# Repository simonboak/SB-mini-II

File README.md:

# SB mini II
A homebrewed Apple II clone. [Read more on the blog post](https://unimplementedtrap.com/sb-mini-ii-apple-ii-clone/)

## Hardware Overview

- The CPU is a standard 65C02 running at near 1.024 MHz (the original Apple II ran at 1.023 for the 60 Hz models), after dividing the 4.096 MHz crystal by 4.
- The 12kB ROM image is placed on the 32k EEPROM. Because there's spare room on this chip a jumper allows for selecting the high or low half of the ROM chip, so I've placed Ardian Black's [Deadtest](https://github.com/misterblack1/appleII_deadtest) program in there.
- 48kB of RAM is accomplished by using one and half 32kB SRAM chips. Figured this was easier to use matching chipd than it was to use a 32kb + 16kB chip.
- Address decoding works exactly like the real Apple II. This was mostly based on the schematics in _Understanding The Apple II_ by Jim Sather.
- In Addition to the I/O slots, this has:
  - Speaker: matching the genuine Apple II
  - Game I/O: as the NE558 quad timer is hard to find, I've [implemented this replacement using a pair of 556 chips](https://github.com/roybaer/ne558_replacement).
  - Keyboard: a Raspberry Pi Pico provides a modern USB interface but electrically it connects to the Apple II in the same way as the original ASCII keyboard did. The Pi can also generate a reset pulse when pressing Control + Print Screen, and also performs a power-on reset for the system. The firmware for this is [in this project here](https://github.com/simonboak/SB-mini-II-Keyboard).
  - Graphics: there is absolutely no onboard hardware for displaying graphics. Instead you'll want to use an [Apple VGA Card](https://github.com/markadev/AppleII-VGA).
- Features deliberately missing:
  - Expansion slots do not provide the DMA, USER 1 or 7M clock signals.
  - The bus is not buffered: with a CMOS design this is less likely to be a problem (although no guarantees for interfacing with cards using 74LS logic).
  - There is no cassette input or output.
- These are the Revision 1 files. Rev 0 was a smaller board with no 5V regulation, only 7 slots and 32k on board RAM. The plan had been to leave out slot 0 and work out how to make full use of a second 32k RAM chip to have the full 64k without needing a language card, however this almost doubled the amount of circuitry needed.

## 3D Printed Case

Combining the design of the Apple II with the ProFile hard disk, the case requires a bit of assembly:

1. Print each piece with the flat side on the print bad (you could print the lid pieces as one if desired)
2. Glue the "tongue" into the slot along the bottom inside edge of the front piece. This will locate into the notch inside the front of the base.
3. Glue the top, front and sides together.
4. For the light pipe it was filled with hot glue to create a diffused lense with the LED glued in behind.
5. The base requires 8x M3 threaded inserts, 2 of which are for the back panel, the rest are the PCB mounts.
6. The 20mm speaker can be taped into the round hole in the base.

### Rear with reset switch

An alernative file for the rear panel of the case is included. This contains a 7mm hole for a suitably sized push button switch.

### Rev 1 Update:

Alternative files are provided for the lid: this greatly reduces the radius of the curve on the front of the case. This should print better and without requiring so much filling and sanding, although it does depart from the styling inspiration of the ProFile hard disk.

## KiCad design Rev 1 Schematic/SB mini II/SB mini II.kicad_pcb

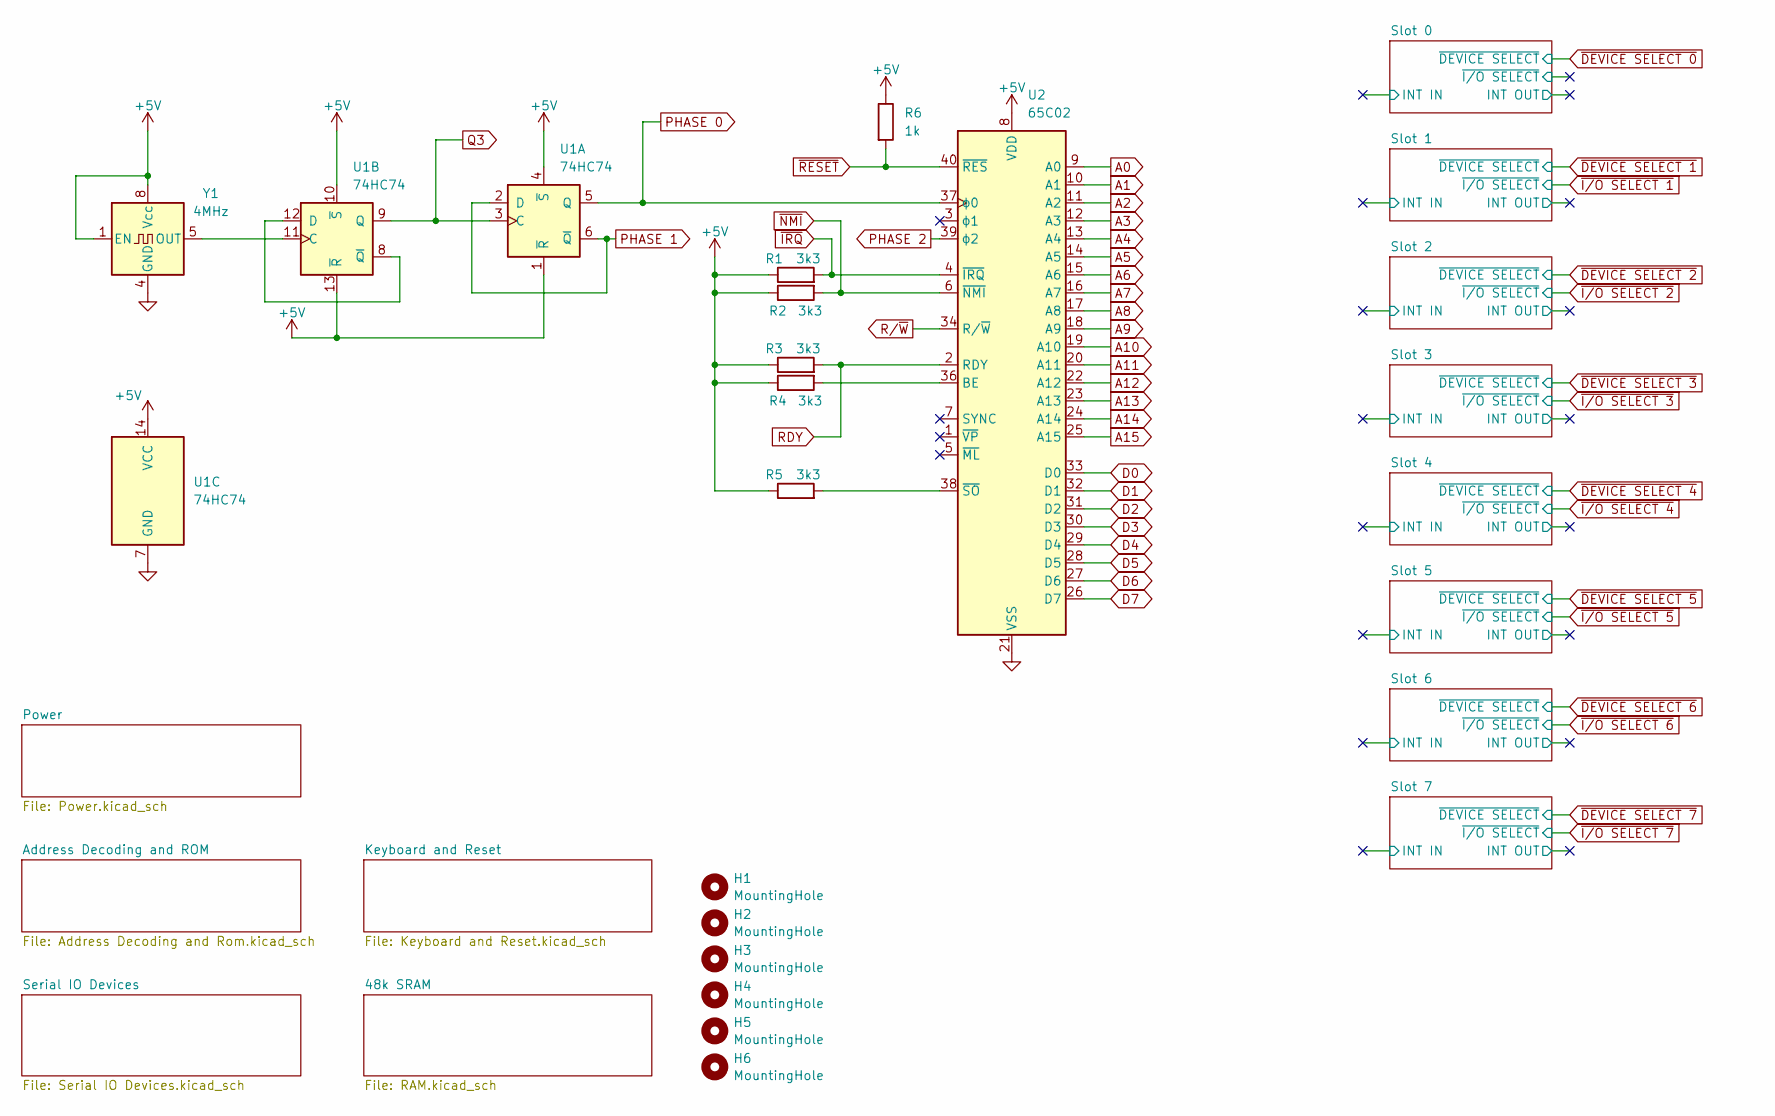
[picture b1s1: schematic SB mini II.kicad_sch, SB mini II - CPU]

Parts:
H1, H2, H3, H4, H5, H6: MountingHole; MountingHole_3.2mm_M3
R1, R2, R3, R4, R5: 3k3; R_Axial_DIN0207_L6.3mm_D2.5mm_P7.62mm_Horizontal
R6: 1k; R_Axial_DIN0207_L6.3mm_D2.5mm_P7.62mm_Horizontal
U1: 74HC74; DIP-14_W7.62mm_LongPads
U2: 65C02; DIP-40_W15.24mm
Y1: 4MHz; Oscillator_DIP-8

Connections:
+5V: R1.1, R2.1, R3.1, R4.1, R5.1, R6.1, U1.1 (~R), U1.4 (~S), U1.10 (~S), U1.13 (~R), U1.14 (VCC), U2.8 (VDD), Y1.1 (EN), Y1.8 (Vcc); also elsewhere on the board
A0: U2.9 (A0); also elsewhere on the board
A1: U2.10 (A1); also elsewhere on the board
A2: U2.11 (A2); also elsewhere on the board
A3: U2.12 (A3); also elsewhere on the board
A4: U2.13 (A4); also elsewhere on the board
A5: U2.14 (A5); also elsewhere on the board
A6: U2.15 (A6); also elsewhere on the board
A7: U2.16 (A7); also elsewhere on the board
A8: U2.17 (A8); also elsewhere on the board
A9: U2.18 (A9); also elsewhere on the board
A10: U2.19 (A10); also elsewhere on the board
A11: U2.20 (A11); also elsewhere on the board
A12: U2.22 (A12); also elsewhere on the board
A13: U2.23 (A13); also elsewhere on the board
A14: U2.24 (A14); also elsewhere on the board
A15: U2.25 (A15); also elsewhere on the board
D0: U2.33 (D0); also elsewhere on the board
D1: U2.32 (D1); also elsewhere on the board
D2: U2.31 (D2); also elsewhere on the board
D3: U2.30 (D3); also elsewhere on the board
D4: U2.29 (D4); also elsewhere on the board
D5: U2.28 (D5); also elsewhere on the board
D6: U2.27 (D6); also elsewhere on the board
D7: U2.26 (D7); also elsewhere on the board
GND: U1.7 (GND), U2.21 (VSS), Y1.4 (GND); also elsewhere on the board
unnamed: U1.11 (C), Y1.5 (OUT)
unnamed: U1.8 (~Q), U1.12 (D)
unnamed: R4.2, U2.36 (BE)
unnamed: R5.2, U2.38 (~SO)
PHASE 0: U1.5 (Q), U2.37 (ϕ0); also elsewhere on the board
PHASE 1: U1.2 (D), U1.6 (~Q); also elsewhere on the board
PHASE 2: U2.39 (ϕ2); also elsewhere on the board
Q3: U1.3 (C), U1.9 (Q); also elsewhere on the board
RDY: R3.2, U2.2 (RDY); also elsewhere on the board
R/~W: U2.34 (R/~W); also elsewhere on the board
~IRQ: R1.2, U2.4 (~IRQ); also elsewhere on the board
~NMI: R2.2, U2.6 (~NMI); also elsewhere on the board
~RESET: R6.2, U2.40 (~RES); also elsewhere on the board

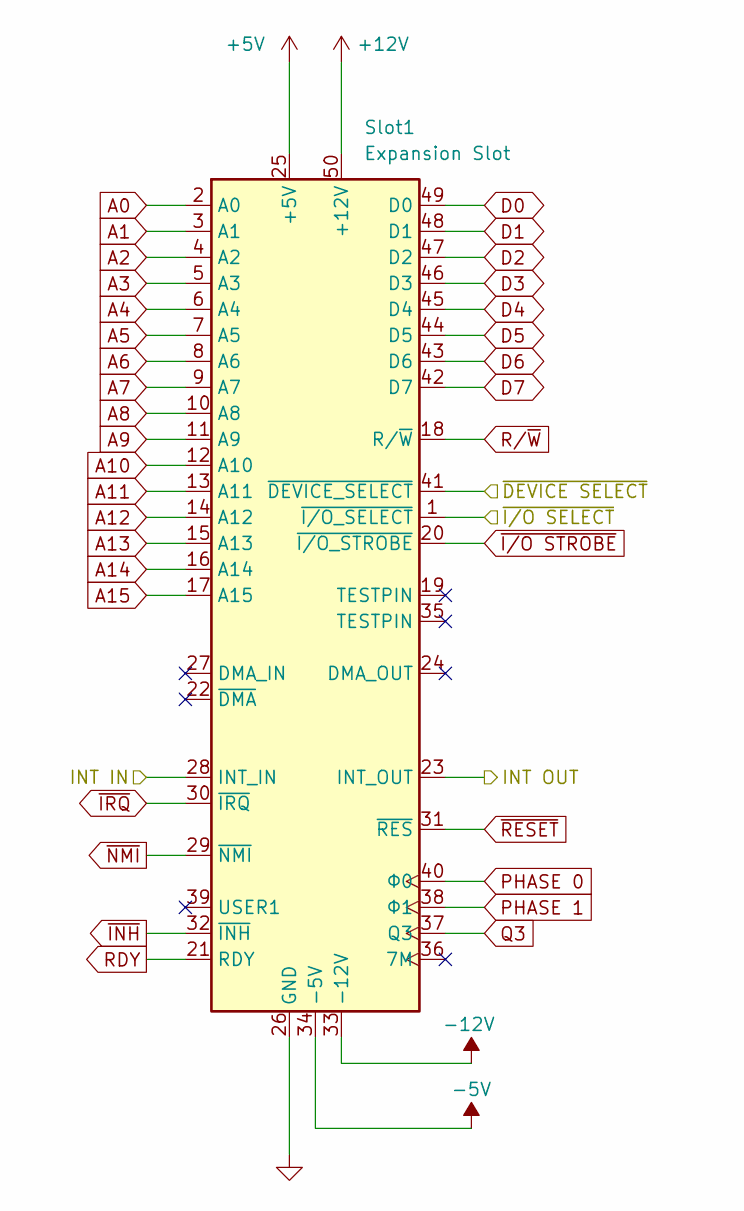
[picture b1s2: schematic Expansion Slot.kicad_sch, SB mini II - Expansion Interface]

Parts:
Slot1: Expansion Slot; EDAC_395-050-520-201_CounterClockwise

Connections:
+5V: Slot1.25 (+5V); also elsewhere on the board
+12V: Slot1.50 (+12V); also elsewhere on the board
-5V: Slot1.34 (-5V); also elsewhere on the board
-12V: Slot1.33 (-12V); also elsewhere on the board
/Slot 1/INT IN: Slot1.28 (INT_IN)
/Slot 1/INT OUT: Slot1.23 (INT_OUT)
A0: Slot1.2 (A0); also elsewhere on the board
A1: Slot1.3 (A1); also elsewhere on the board
A2: Slot1.4 (A2); also elsewhere on the board
A3: Slot1.5 (A3); also elsewhere on the board
A4: Slot1.6 (A4); also elsewhere on the board
A5: Slot1.7 (A5); also elsewhere on the board
A6: Slot1.8 (A6); also elsewhere on the board
A7: Slot1.9 (A7); also elsewhere on the board
A8: Slot1.10 (A8); also elsewhere on the board
A9: Slot1.11 (A9); also elsewhere on the board
A10: Slot1.12 (A10); also elsewhere on the board
A11: Slot1.13 (A11); also elsewhere on the board
A12: Slot1.14 (A12); also elsewhere on the board
A13: Slot1.15 (A13); also elsewhere on the board
A14: Slot1.16 (A14); also elsewhere on the board
A15: Slot1.17 (A15); also elsewhere on the board
D0: Slot1.49 (D0); also elsewhere on the board
D1: Slot1.48 (D1); also elsewhere on the board
D2: Slot1.47 (D2); also elsewhere on the board
D3: Slot1.46 (D3); also elsewhere on the board
D4: Slot1.45 (D4); also elsewhere on the board
D5: Slot1.44 (D5); also elsewhere on the board
D6: Slot1.43 (D6); also elsewhere on the board
D7: Slot1.42 (D7); also elsewhere on the board
GND: Slot1.26 (GND); also elsewhere on the board
PHASE 0: Slot1.40 (Φ0); also elsewhere on the board
PHASE 1: Slot1.38 (Φ1); also elsewhere on the board
Q3: Slot1.37 (Q3); also elsewhere on the board
RDY: Slot1.21 (RDY); also elsewhere on the board
R/~W: Slot1.18 (R/~W); also elsewhere on the board
~DEVICE SELECT 1: Slot1.41 (~DEVICE_SELECT); also elsewhere on the board
~INH: Slot1.32 (~INH); also elsewhere on the board
~IRQ: Slot1.30 (~IRQ); also elsewhere on the board
~I/O SELECT 1: Slot1.1 (~I/O_SELECT); also elsewhere on the board
~I/O STROBE: Slot1.20 (~I/O_STROBE); also elsewhere on the board
~NMI: Slot1.29 (~NMI); also elsewhere on the board
~RESET: Slot1.31 (~RES); also elsewhere on the board

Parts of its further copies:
Slot0, Slot2, Slot3, Slot4, Slot5, Slot6, Slot7: Expansion Slot; EDAC_395-050-520-201_CounterClockwise

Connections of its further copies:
+5V: Slot0.25 (+5V), Slot2.25 (+5V), Slot3.25 (+5V), Slot4.25 (+5V), Slot5.25 (+5V), Slot6.25 (+5V), Slot7.25 (+5V); also elsewhere on the board
+12V: Slot0.50 (+12V), Slot2.50 (+12V), Slot3.50 (+12V), Slot4.50 (+12V), Slot5.50 (+12V), Slot6.50 (+12V), Slot7.50 (+12V); also elsewhere on the board
-5V: Slot0.34 (-5V), Slot2.34 (-5V), Slot3.34 (-5V), Slot4.34 (-5V), Slot5.34 (-5V), Slot6.34 (-5V), Slot7.34 (-5V); also elsewhere on the board
-12V: Slot0.33 (-12V), Slot2.33 (-12V), Slot3.33 (-12V), Slot4.33 (-12V), Slot5.33 (-12V), Slot6.33 (-12V), Slot7.33 (-12V); also elsewhere on the board
/Slot 0/INT IN: Slot0.28 (INT_IN)
/Slot 0/INT OUT: Slot0.23 (INT_OUT)
/Slot 0/~I/O SELECT: Slot0.1 (~I/O_SELECT)
/Slot 2/INT IN: Slot2.28 (INT_IN)
/Slot 2/INT OUT: Slot2.23 (INT_OUT)
/Slot 3/INT IN: Slot4.28 (INT_IN)
/Slot 3/INT OUT: Slot4.23 (INT_OUT)
/Slot 4/INT IN: Slot5.28 (INT_IN)
/Slot 4/INT OUT: Slot5.23 (INT_OUT)
/Slot 5/INT IN: Slot3.28 (INT_IN)
/Slot 5/INT OUT: Slot3.23 (INT_OUT)
/Slot 6/INT IN: Slot6.28 (INT_IN)
/Slot 6/INT OUT: Slot6.23 (INT_OUT)
/Slot 7/INT IN: Slot7.28 (INT_IN)
/Slot 7/INT OUT: Slot7.23 (INT_OUT)
A0: Slot0.2 (A0), Slot2.2 (A0), Slot3.2 (A0), Slot4.2 (A0), Slot5.2 (A0), Slot6.2 (A0), Slot7.2 (A0); also elsewhere on the board
A1: Slot0.3 (A1), Slot2.3 (A1), Slot3.3 (A1), Slot4.3 (A1), Slot5.3 (A1), Slot6.3 (A1), Slot7.3 (A1); also elsewhere on the board
A2: Slot0.4 (A2), Slot2.4 (A2), Slot3.4 (A2), Slot4.4 (A2), Slot5.4 (A2), Slot6.4 (A2), Slot7.4 (A2); also elsewhere on the board
A3: Slot0.5 (A3), Slot2.5 (A3), Slot3.5 (A3), Slot4.5 (A3), Slot5.5 (A3), Slot6.5 (A3), Slot7.5 (A3); also elsewhere on the board
A4: Slot0.6 (A4), Slot2.6 (A4), Slot3.6 (A4), Slot4.6 (A4), Slot5.6 (A4), Slot6.6 (A4), Slot7.6 (A4); also elsewhere on the board
A5: Slot0.7 (A5), Slot2.7 (A5), Slot3.7 (A5), Slot4.7 (A5), Slot5.7 (A5), Slot6.7 (A5), Slot7.7 (A5); also elsewhere on the board
A6: Slot0.8 (A6), Slot2.8 (A6), Slot3.8 (A6), Slot4.8 (A6), Slot5.8 (A6), Slot6.8 (A6), Slot7.8 (A6); also elsewhere on the board
A7: Slot0.9 (A7), Slot2.9 (A7), Slot3.9 (A7), Slot4.9 (A7), Slot5.9 (A7), Slot6.9 (A7), Slot7.9 (A7); also elsewhere on the board
A8: Slot0.10 (A8), Slot2.10 (A8), Slot3.10 (A8), Slot4.10 (A8), Slot5.10 (A8), Slot6.10 (A8), Slot7.10 (A8); also elsewhere on the board
A9: Slot0.11 (A9), Slot2.11 (A9), Slot3.11 (A9), Slot4.11 (A9), Slot5.11 (A9), Slot6.11 (A9), Slot7.11 (A9); also elsewhere on the board
A10: Slot0.12 (A10), Slot2.12 (A10), Slot3.12 (A10), Slot4.12 (A10), Slot5.12 (A10), Slot6.12 (A10), Slot7.12 (A10); also elsewhere on the board
A11: Slot0.13 (A11), Slot2.13 (A11), Slot3.13 (A11), Slot4.13 (A11), Slot5.13 (A11), Slot6.13 (A11), Slot7.13 (A11); also elsewhere on the board
A12: Slot0.14 (A12), Slot2.14 (A12), Slot3.14 (A12), Slot4.14 (A12), Slot5.14 (A12), Slot6.14 (A12), Slot7.14 (A12); also elsewhere on the board
A13: Slot0.15 (A13), Slot2.15 (A13), Slot3.15 (A13), Slot4.15 (A13), Slot5.15 (A13), Slot6.15 (A13), Slot7.15 (A13); also elsewhere on the board
A14: Slot0.16 (A14), Slot2.16 (A14), Slot3.16 (A14), Slot4.16 (A14), Slot5.16 (A14), Slot6.16 (A14), Slot7.16 (A14); also elsewhere on the board
A15: Slot0.17 (A15), Slot2.17 (A15), Slot3.17 (A15), Slot4.17 (A15), Slot5.17 (A15), Slot6.17 (A15), Slot7.17 (A15); also elsewhere on the board
D0: Slot0.49 (D0), Slot2.49 (D0), Slot3.49 (D0), Slot4.49 (D0), Slot5.49 (D0), Slot6.49 (D0), Slot7.49 (D0); also elsewhere on the board
D1: Slot0.48 (D1), Slot2.48 (D1), Slot3.48 (D1), Slot4.48 (D1), Slot5.48 (D1), Slot6.48 (D1), Slot7.48 (D1); also elsewhere on the board
D2: Slot0.47 (D2), Slot2.47 (D2), Slot3.47 (D2), Slot4.47 (D2), Slot5.47 (D2), Slot6.47 (D2), Slot7.47 (D2); also elsewhere on the board
D3: Slot0.46 (D3), Slot2.46 (D3), Slot3.46 (D3), Slot4.46 (D3), Slot5.46 (D3), Slot6.46 (D3), Slot7.46 (D3); also elsewhere on the board
D4: Slot0.45 (D4), Slot2.45 (D4), Slot3.45 (D4), Slot4.45 (D4), Slot5.45 (D4), Slot6.45 (D4), Slot7.45 (D4); also elsewhere on the board
D5: Slot0.44 (D5), Slot2.44 (D5), Slot3.44 (D5), Slot4.44 (D5), Slot5.44 (D5), Slot6.44 (D5), Slot7.44 (D5); also elsewhere on the board
D6: Slot0.43 (D6), Slot2.43 (D6), Slot3.43 (D6), Slot4.43 (D6), Slot5.43 (D6), Slot6.43 (D6), Slot7.43 (D6); also elsewhere on the board
D7: Slot0.42 (D7), Slot2.42 (D7), Slot3.42 (D7), Slot4.42 (D7), Slot5.42 (D7), Slot6.42 (D7), Slot7.42 (D7); also elsewhere on the board
GND: Slot0.26 (GND), Slot2.26 (GND), Slot3.26 (GND), Slot4.26 (GND), Slot5.26 (GND), Slot6.26 (GND), Slot7.26 (GND); also elsewhere on the board
PHASE 0: Slot0.40 (Φ0), Slot2.40 (Φ0), Slot3.40 (Φ0), Slot4.40 (Φ0), Slot5.40 (Φ0), Slot6.40 (Φ0), Slot7.40 (Φ0); also elsewhere on the board
PHASE 1: Slot0.38 (Φ1), Slot2.38 (Φ1), Slot3.38 (Φ1), Slot4.38 (Φ1), Slot5.38 (Φ1), Slot6.38 (Φ1), Slot7.38 (Φ1); also elsewhere on the board
Q3: Slot0.37 (Q3), Slot2.37 (Q3), Slot3.37 (Q3), Slot4.37 (Q3), Slot5.37 (Q3), Slot6.37 (Q3), Slot7.37 (Q3); also elsewhere on the board
RDY: Slot0.21 (RDY), Slot2.21 (RDY), Slot3.21 (RDY), Slot4.21 (RDY), Slot5.21 (RDY), Slot6.21 (RDY), Slot7.21 (RDY); also elsewhere on the board
R/~W: Slot0.18 (R/~W), Slot2.18 (R/~W), Slot3.18 (R/~W), Slot4.18 (R/~W), Slot5.18 (R/~W), Slot6.18 (R/~W), Slot7.18 (R/~W); also elsewhere on the board
~DEVICE SELECT 0: Slot0.41 (~DEVICE_SELECT); also elsewhere on the board
~DEVICE SELECT 2: Slot2.41 (~DEVICE_SELECT); also elsewhere on the board
~DEVICE SELECT 3: Slot4.41 (~DEVICE_SELECT); also elsewhere on the board
~DEVICE SELECT 4: Slot5.41 (~DEVICE_SELECT); also elsewhere on the board
~DEVICE SELECT 5: Slot3.41 (~DEVICE_SELECT); also elsewhere on the board
~DEVICE SELECT 6: Slot6.41 (~DEVICE_SELECT); also elsewhere on the board
~DEVICE SELECT 7: Slot7.41 (~DEVICE_SELECT); also elsewhere on the board
~INH: Slot0.32 (~INH), Slot2.32 (~INH), Slot3.32 (~INH), Slot4.32 (~INH), Slot5.32 (~INH), Slot6.32 (~INH), Slot7.32 (~INH); also elsewhere on the board
~IRQ: Slot0.30 (~IRQ), Slot2.30 (~IRQ), Slot3.30 (~IRQ), Slot4.30 (~IRQ), Slot5.30 (~IRQ), Slot6.30 (~IRQ), Slot7.30 (~IRQ); also elsewhere on the board
~I/O SELECT 2: Slot2.1 (~I/O_SELECT); also elsewhere on the board
~I/O SELECT 3: Slot4.1 (~I/O_SELECT); also elsewhere on the board
~I/O SELECT 4: Slot5.1 (~I/O_SELECT); also elsewhere on the board
~I/O SELECT 5: Slot3.1 (~I/O_SELECT); also elsewhere on the board
~I/O SELECT 6: Slot6.1 (~I/O_SELECT); also elsewhere on the board
~I/O SELECT 7: Slot7.1 (~I/O_SELECT); also elsewhere on the board
~I/O STROBE: Slot0.20 (~I/O_STROBE), Slot2.20 (~I/O_STROBE), Slot3.20 (~I/O_STROBE), Slot4.20 (~I/O_STROBE), Slot5.20 (~I/O_STROBE), Slot6.20 (~I/O_STROBE), Slot7.20 (~I/O_STROBE); also elsewhere on the board
~NMI: Slot0.29 (~NMI), Slot2.29 (~NMI), Slot3.29 (~NMI), Slot4.29 (~NMI), Slot5.29 (~NMI), Slot6.29 (~NMI), Slot7.29 (~NMI); also elsewhere on the board
~RESET: Slot0.31 (~RES), Slot2.31 (~RES), Slot3.31 (~RES), Slot4.31 (~RES), Slot5.31 (~RES), Slot6.31 (~RES), Slot7.31 (~RES); also elsewhere on the board

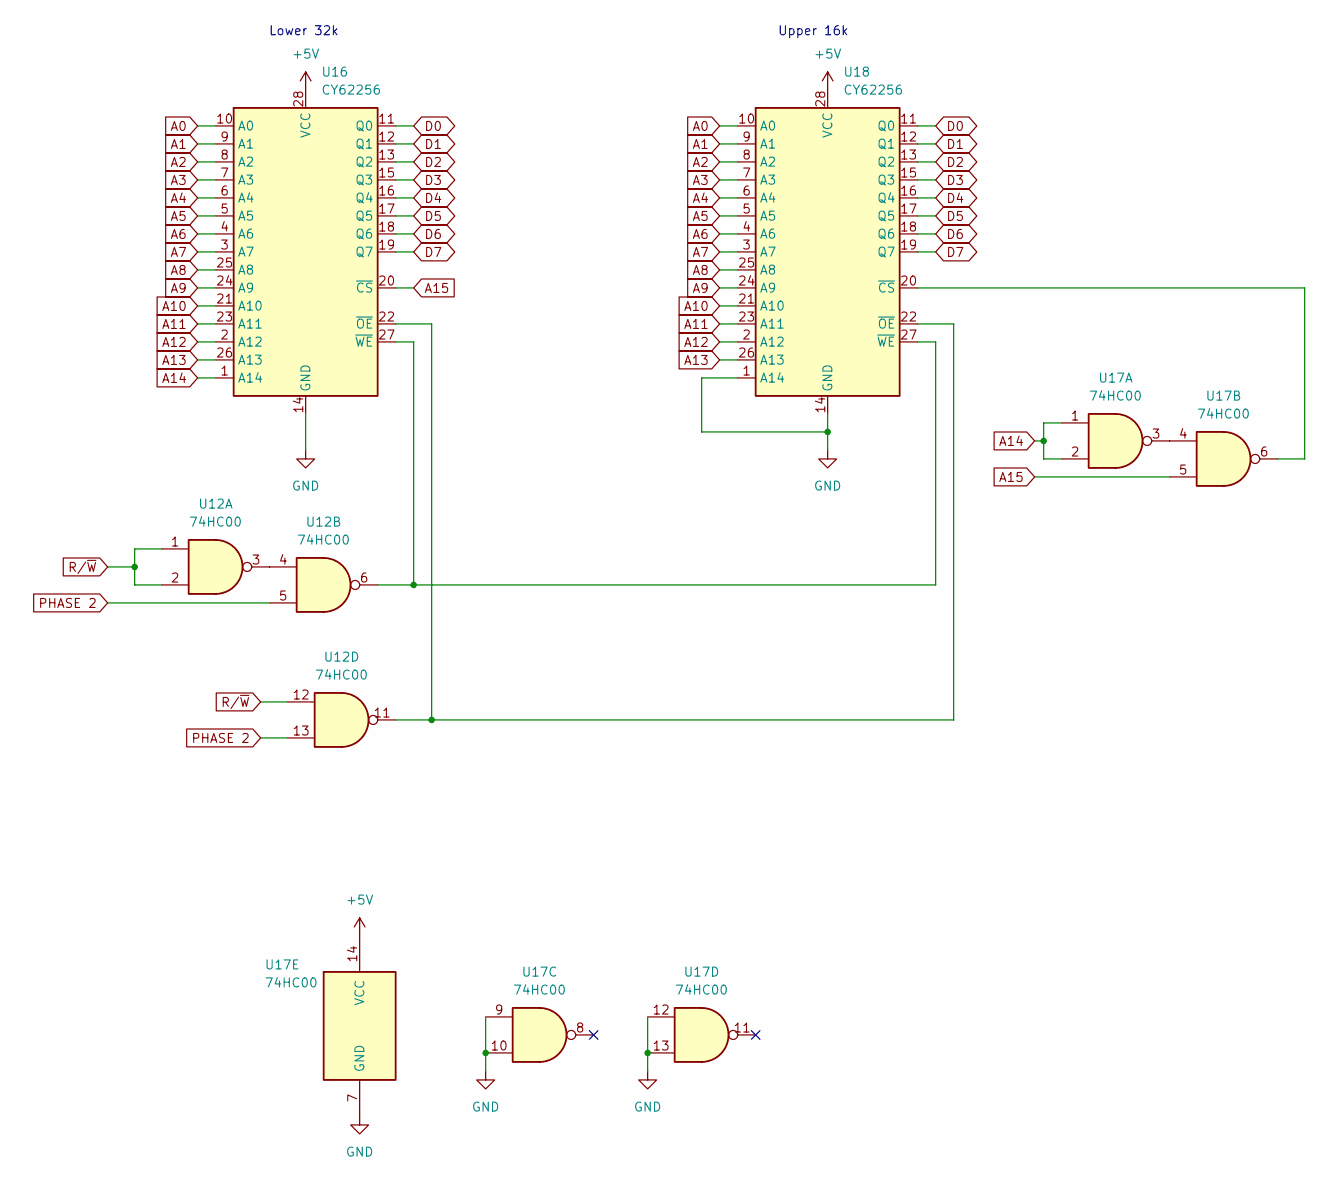
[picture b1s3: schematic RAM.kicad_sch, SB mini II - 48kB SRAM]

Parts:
U12, U17: 74HC00; DIP-14_W7.62mm_LongPads
U16, U18: CY62256; DIP-28_W7.62mm_LongPads

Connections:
+5V: U16.28 (VCC), U17.14 (VCC), U18.28 (VCC); also elsewhere on the board
A0: U16.10 (A0), U18.10 (A0); also elsewhere on the board
A1: U16.9 (A1), U18.9 (A1); also elsewhere on the board
A2: U16.8 (A2), U18.8 (A2); also elsewhere on the board
A3: U16.7 (A3), U18.7 (A3); also elsewhere on the board
A4: U16.6 (A4), U18.6 (A4); also elsewhere on the board
A5: U16.5 (A5), U18.5 (A5); also elsewhere on the board
A6: U16.4 (A6), U18.4 (A6); also elsewhere on the board
A7: U16.3 (A7), U18.3 (A7); also elsewhere on the board
A8: U16.25 (A8), U18.25 (A8); also elsewhere on the board
A9: U16.24 (A9), U18.24 (A9); also elsewhere on the board
A10: U16.21 (A10), U18.21 (A10); also elsewhere on the board
A11: U16.23 (A11), U18.23 (A11); also elsewhere on the board
A12: U16.2 (A12), U18.2 (A12); also elsewhere on the board
A13: U16.26 (A13), U18.26 (A13); also elsewhere on the board
A14: U16.1 (A14), U17.1, U17.2; also elsewhere on the board
A15: U16.20 (~CS), U17.5; also elsewhere on the board
D0: U16.11 (Q0), U18.11 (Q0); also elsewhere on the board
D1: U16.12 (Q1), U18.12 (Q1); also elsewhere on the board
D2: U16.13 (Q2), U18.13 (Q2); also elsewhere on the board
D3: U16.15 (Q3), U18.15 (Q3); also elsewhere on the board
D4: U16.16 (Q4), U18.16 (Q4); also elsewhere on the board
D5: U16.17 (Q5), U18.17 (Q5); also elsewhere on the board
D6: U16.18 (Q6), U18.18 (Q6); also elsewhere on the board
D7: U16.19 (Q7), U18.19 (Q7); also elsewhere on the board
GND: U16.14 (GND), U17.7 (GND), U17.9, U17.10, U17.12, U17.13, U18.1 (A14), U18.14 (GND); also elsewhere on the board
unnamed: U12.3, U12.4
unnamed: U12.11, U16.22 (~OE), U18.22 (~OE)
unnamed: U12.6, U16.27 (~WE), U18.27 (~WE)
unnamed: U17.3, U17.4
unnamed: U17.6, U18.20 (~CS)
PHASE 2: U12.5, U12.13; also elsewhere on the board
R/~W: U12.1, U12.2, U12.12; also elsewhere on the board

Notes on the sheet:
Upper 16k
Lower 32k

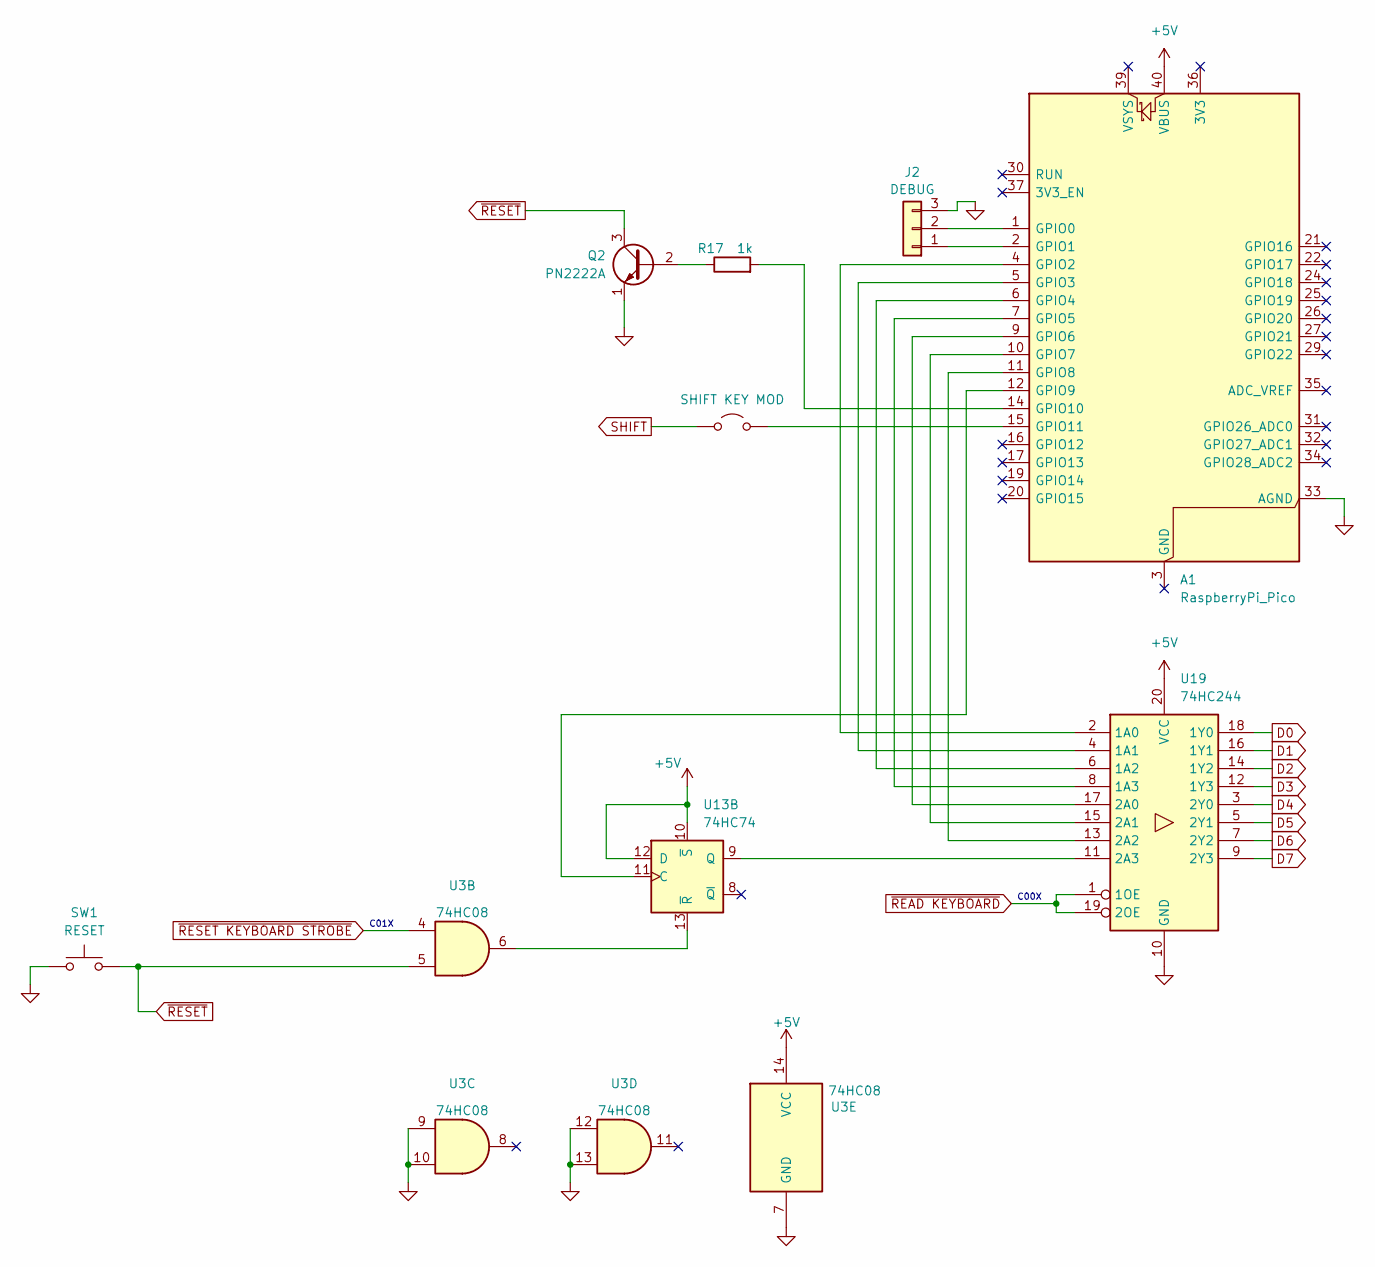
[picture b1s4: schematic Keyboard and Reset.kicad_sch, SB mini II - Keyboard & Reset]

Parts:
A1: RaspberryPi_Pico; RaspberryPi_Pico_Common_Unspecified
J2: DEBUG; PinHeader_1x03_P2.54mm_Vertical
JP2: SHIFT KEY MOD; TestPoint_2Pads_Pitch2.54mm_Drill0.8mm
Q2: PN2222A; TO-92L_HandSolder
R17: 1k; R_Axial_DIN0207_L6.3mm_D2.5mm_P7.62mm_Horizontal
SW1: RESET; SW_PUSH_1P1T_6x3.5mm_H5.0_APEM_MJTP1250
U3: 74HC08; DIP-14_W7.62mm_LongPads
U13: 74HC74; DIP-14_W7.62mm_LongPads
U19: 74HC244; DIP-20_W7.62mm_LongPads

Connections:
+5V: A1.40 (VBUS), U3.14 (VCC), U13.10 (~S), U13.12 (D), U19.20 (VCC); also elsewhere on the board
D0: U19.18 (1Y0); also elsewhere on the board
D1: U19.16 (1Y1); also elsewhere on the board
D2: U19.14 (1Y2); also elsewhere on the board
D3: U19.12 (1Y3); also elsewhere on the board
D4: U19.3 (2Y0); also elsewhere on the board
D5: U19.5 (2Y1); also elsewhere on the board
D6: U19.7 (2Y2); also elsewhere on the board
D7: U19.9 (2Y3); also elsewhere on the board
GND: A1.33 (AGND), J2.3, Q2.1 (E), SW1.1, U3.7 (GND), U3.9, U3.10, U3.12, U3.13, U19.10 (GND); also elsewhere on the board
unnamed: A1.1 (GPIO0), J2.2
unnamed: A1.2 (GPIO1), J2.1
unnamed: A1.4 (GPIO2), U19.2 (1A0)
unnamed: A1.5 (GPIO3), U19.4 (1A1)
unnamed: A1.6 (GPIO4), U19.6 (1A2)
unnamed: A1.7 (GPIO5), U19.8 (1A3)
unnamed: A1.9 (GPIO6), U19.17 (2A0)
unnamed: A1.10 (GPIO7), U19.15 (2A1)
unnamed: A1.11 (GPIO8), U19.13 (2A2)
unnamed: A1.12 (GPIO9), U13.11 (C)
unnamed: A1.14 (GPIO10), R17.2
unnamed: A1.15 (GPIO11), JP2.2 (B)
unnamed: Q2.2 (B), R17.1
unnamed: U13.9 (Q), U19.11 (2A3)
unnamed: U3.6, U13.13 (~R)
SHIFT: JP2.1 (A); also elsewhere on the board
~READ KEYBOARD: U19.1 (1OE), U19.19 (2OE); also elsewhere on the board
~RESET KEYBOARD STROBE: U3.4; also elsewhere on the board
~RESET: Q2.3 (C), SW1.2, U3.5; also elsewhere on the board

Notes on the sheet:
C00X
C01X

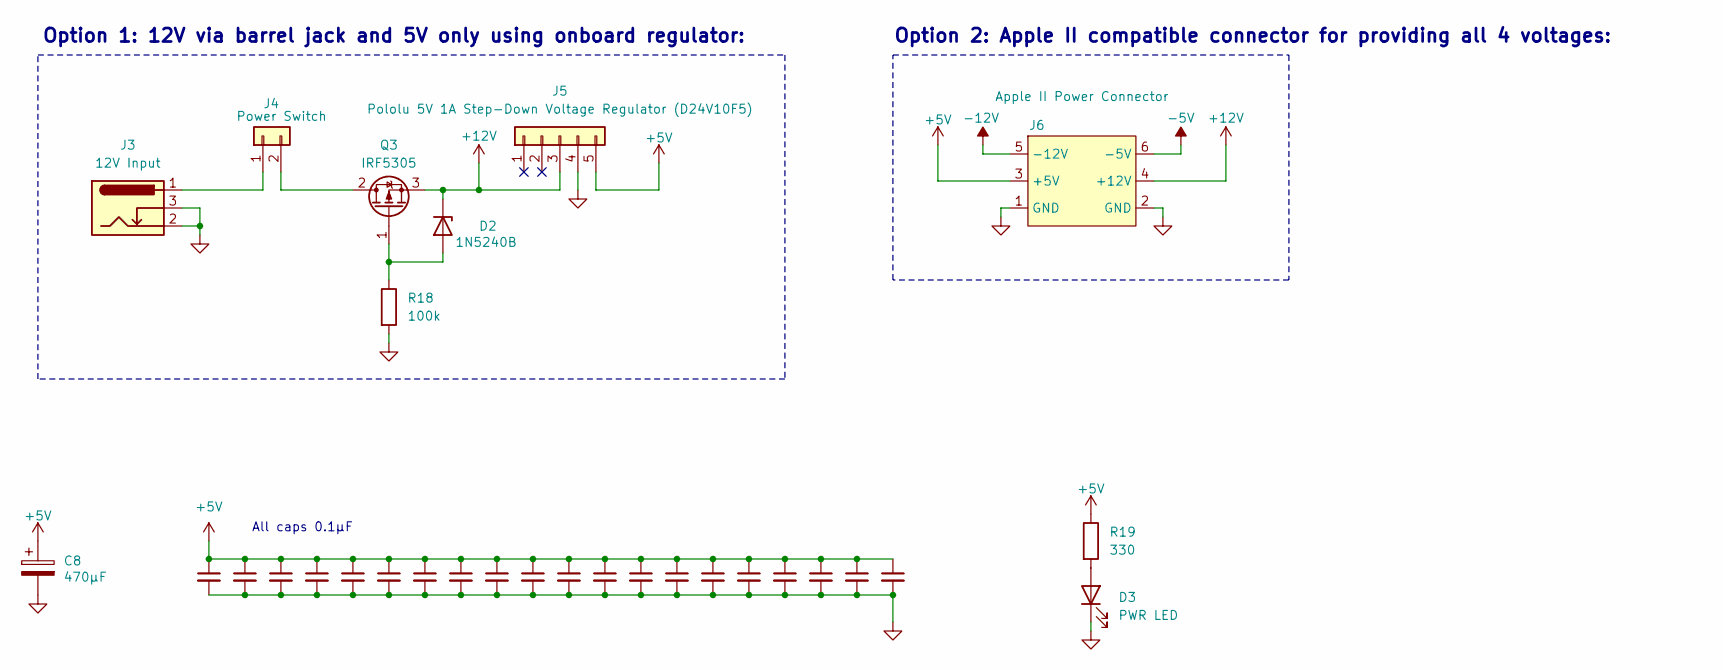
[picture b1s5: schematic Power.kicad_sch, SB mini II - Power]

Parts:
C8: 470µF; CP_Radial_D6.3mm_P2.50mm
C9, C10, C11, C12, C13, C14, C15, C16, C17, C18, C19, C20, C21, C22, C23, C24, C25, C26, C27, C28: 0.1µF; R_Axial_DIN0204_L3.6mm_D1.6mm_P5.08mm_Horizontal
D2: 1N5240B; D_DO-41_SOD81_P10.16mm_Horizontal
D3: PWR LED; LED_D5.0mm
J3: 12V Input; BarrelJack_Horizontal
J4: Power Switch; TerminalBlock_MaiXu_MX126-5.0-02P_1x02_P5.00mm
J5: Pololu 5V 1A Step-Down Voltage Regulator (D24V10F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; PinSocket_1x05_P2.54mm_Vertical
J6: Apple II Power Connector; 1-640520-0_Power_Connector
Q3: IRF5305; TO-220-3_Vertical
R18: 100k; R_Axial_DIN0207_L6.3mm_D2.5mm_P7.62mm_Horizontal
R19: 330; R_Axial_DIN0207_L6.3mm_D2.5mm_P7.62mm_Horizontal

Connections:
+5V: C8.1, C9.1, C10.1, C11.1, C12.1, C13.1, C14.1, C15.1, C16.1, C17.1, C18.1, C19.1, C20.1, C21.1, C22.1, C23.1, C24.1, C25.1, C26.1, C27.1, C28.1, J5.5, J6.3 (+5V), R19.1; also elsewhere on the board
+12V: D2.1 (K), J5.3, J6.4 (+12V), Q3.3 (S); also elsewhere on the board
-5V: J6.6 (-5V); also elsewhere on the board
-12V: J6.5 (-12V); also elsewhere on the board
GND: C8.2, C9.2, C10.2, C11.2, C12.2, C13.2, C14.2, C15.2, C16.2, C17.2, C18.2, C19.2, C20.2, C21.2, C22.2, C23.2, C24.2, C25.2, C26.2, C27.2, C28.2, D3.1 (K), J3.2, J3.3, J5.4, J6.1 (GND), J6.2 (GND), R18.2; also elsewhere on the board
unnamed: D2.2 (A), Q3.1 (G), R18.1
unnamed: D3.2 (A), R19.2
unnamed: J3.1, J4.1
unnamed: J4.2, Q3.2 (D)

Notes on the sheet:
All caps 0.1µF
Option 1: 12V via barrel jack and 5V only using onboard regulator:
Option 2: Apple II compatible connector for providing all 4 voltages:

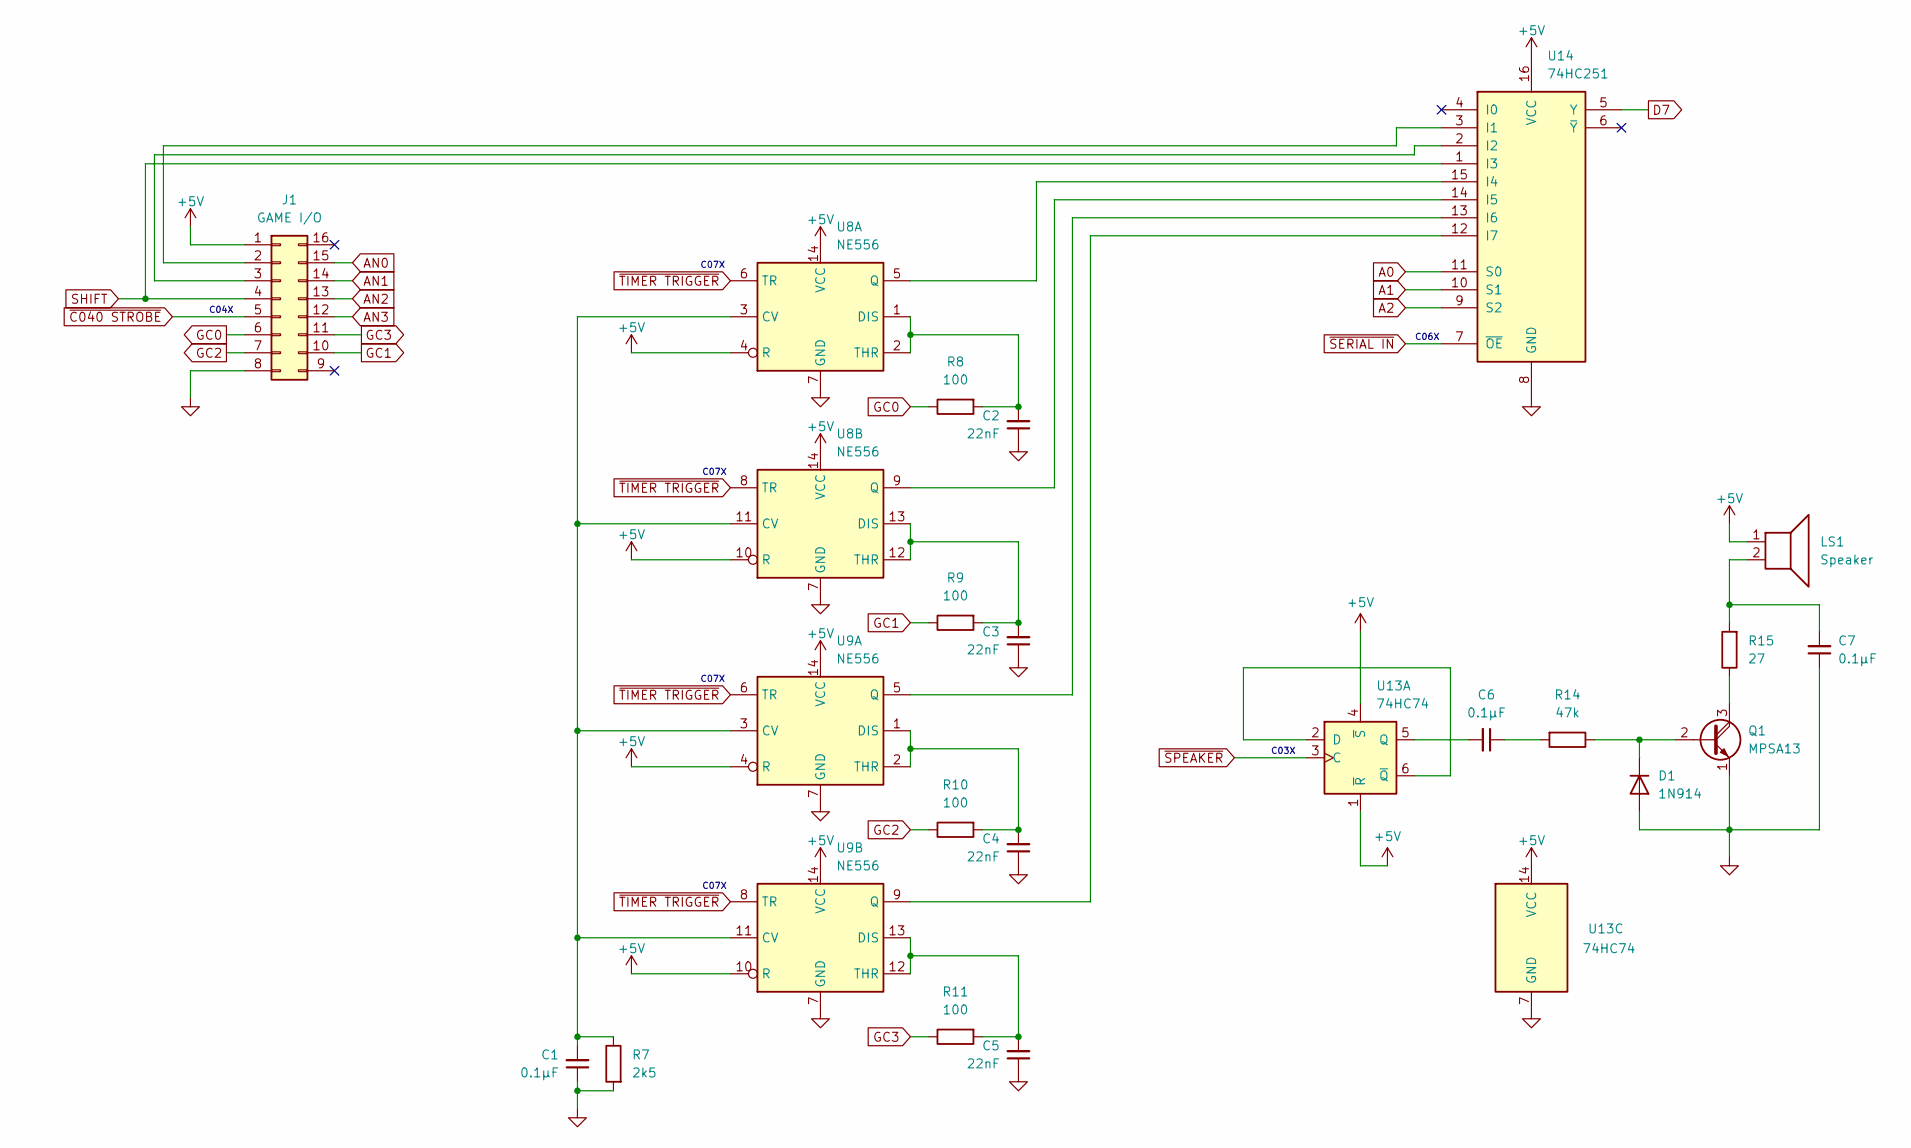
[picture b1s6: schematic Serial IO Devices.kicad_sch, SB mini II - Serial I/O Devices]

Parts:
C1, C6, C7: 0.1µF; R_Axial_DIN0204_L3.6mm_D1.6mm_P5.08mm_Horizontal
C2, C3, C4, C5: 22nF; R_Axial_DIN0204_L3.6mm_D1.6mm_P5.08mm_Horizontal
D1: 1N914; D_DO-35_SOD27_P7.62mm_Horizontal
J1: GAME I/O; DIP-16_W7.62mm_Socket_LongPads
LS1: Speaker; Molex_KK-254_AE-6410-02A_1x02_P2.54mm_Vertical
Q1: MPSA13; TO-92L_HandSolder
R7: 2k5; R_Axial_DIN0207_L6.3mm_D2.5mm_P7.62mm_Horizontal
R8, R9, R10, R11: 100; R_Axial_DIN0207_L6.3mm_D2.5mm_P7.62mm_Horizontal
R14: 47k; R_Axial_DIN0207_L6.3mm_D2.5mm_P7.62mm_Horizontal
R15: 27; R_Axial_DIN0207_L6.3mm_D2.5mm_P7.62mm_Horizontal
U8, U9: NE556; DIP-14_W7.62mm_LongPads
U13: 74HC74; DIP-14_W7.62mm_LongPads
U14: 74HC251; DIP-16_W7.62mm_LongPads

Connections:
+5V: J1.1, LS1.1, U8.4 (R), U8.10 (R), U8.14 (VCC), U9.4 (R), U9.10 (R), U9.14 (VCC), U13.1 (~R), U13.4 (~S), U13.14 (VCC), U14.16 (VCC); also elsewhere on the board
A0: U14.11 (S0); also elsewhere on the board
A1: U14.10 (S1); also elsewhere on the board
A2: U14.9 (S2); also elsewhere on the board
AN0: J1.15; also elsewhere on the board
AN1: J1.14; also elsewhere on the board
AN2: J1.13; also elsewhere on the board
AN3: J1.12; also elsewhere on the board
D7: U14.5 (Y); also elsewhere on the board
GC0: J1.6, R8.1
GC1: J1.10, R9.1
GC2: J1.7, R10.1
GC3: J1.11, R11.1
GND: C1.1, C2.1, C3.1, C4.1, C5.1, C7.1, D1.2 (A), J1.8, Q1.1 (E), R7.2, U8.7 (GND), U9.7 (GND), U13.7 (GND), U14.8 (GND); also elsewhere on the board
unnamed: C6.1, R14.2
unnamed: C7.2, LS1.2, R15.2
unnamed: D1.1 (K), Q1.2 (B), R14.1
unnamed: J1.2, U14.3 (I1)
unnamed: J1.3, U14.2 (I2)
unnamed: Q1.3 (C), R15.1
unnamed: C1.2, R7.1, U8.3 (CV), U8.11 (CV), U9.3 (CV), U9.11 (CV)
unnamed: C2.2, R8.2, U8.1 (DIS), U8.2 (THR)
unnamed: C3.2, R9.2, U8.12 (THR), U8.13 (DIS)
unnamed: C4.2, R10.2, U9.1 (DIS), U9.2 (THR)
unnamed: C5.2, R11.2, U9.12 (THR), U9.13 (DIS)
unnamed: U13.2 (D), U13.6 (~Q)
unnamed: C6.2, U13.5 (Q)
unnamed: U8.5 (Q), U14.15 (I4)
unnamed: U8.9 (Q), U14.14 (I5)
unnamed: U9.5 (Q), U14.13 (I6)
unnamed: U9.9 (Q), U14.12 (I7)
SHIFT: J1.4, U14.1 (I3); also elsewhere on the board
~C040 STROBE: J1.5; also elsewhere on the board
~SERIAL IN: U14.7 (~OE); also elsewhere on the board
~SPEAKER: U13.3 (C); also elsewhere on the board
~TIMER TRIGGER: U8.6 (TR), U8.8 (TR), U9.6 (TR), U9.8 (TR); also elsewhere on the board

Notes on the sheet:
C07X
C03X
C06X
C04X
